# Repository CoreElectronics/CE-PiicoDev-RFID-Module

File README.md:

# PiicoDev® RFID Module

This is the repo for the Core Electronics [PiicoDev RFID Module](https://core-electronics.com.au/catalog/product/view/sku/CE08086).

The PiicoDev® RFID Module will get you started with reading (and writing) RFID tags. Use unique tag IDs to identify users, track your equipment, or make your own vending machine. Getting started is easy - there's no need for soldering, and great PiicoDev guides for Python / MicroPython. If you prefer to go freestyle, each RFID module features a standard breakout header for breadboarding or wires, and the small size makes it ideal for compact projects. This module is compatible with modern RFID / NFC tags: NTAG213, NTAG203 and Classic (aka. Mifare) tags. That means you can not only read the tag ID, but also read or write data to the tag. For more advanced projects, you can connect up to four RFID modules on a single bus. Each device address is selectable using the address switch (labelled ASW) which can select addresses from 0x2C (factory default) to 0x2F.

**Features**

- Small size to fit your project
- Read IDs and Read/Write data to your tag
- Connect up to four RFID modules on the same bus
- Great guides to get you started
- PiicoDev connector, compatible with Qwiic and STEMMA QT (3.3V only)
- 2.54mm breakout for breadboarding/prototyping
- Manufactured and supported in Australia by Core Electronics

## License
This project is open source - please review the LICENSE.md file for further licensing information.

If you have any technical questions, or concerns about licensing, please contact technical support on the [Core Electronics forums](https://forum.core-electronics.com.au/).

*\"PiicoDev\" and the PiicoDev logo are trademarks of Core Electronics Pty Ltd.*

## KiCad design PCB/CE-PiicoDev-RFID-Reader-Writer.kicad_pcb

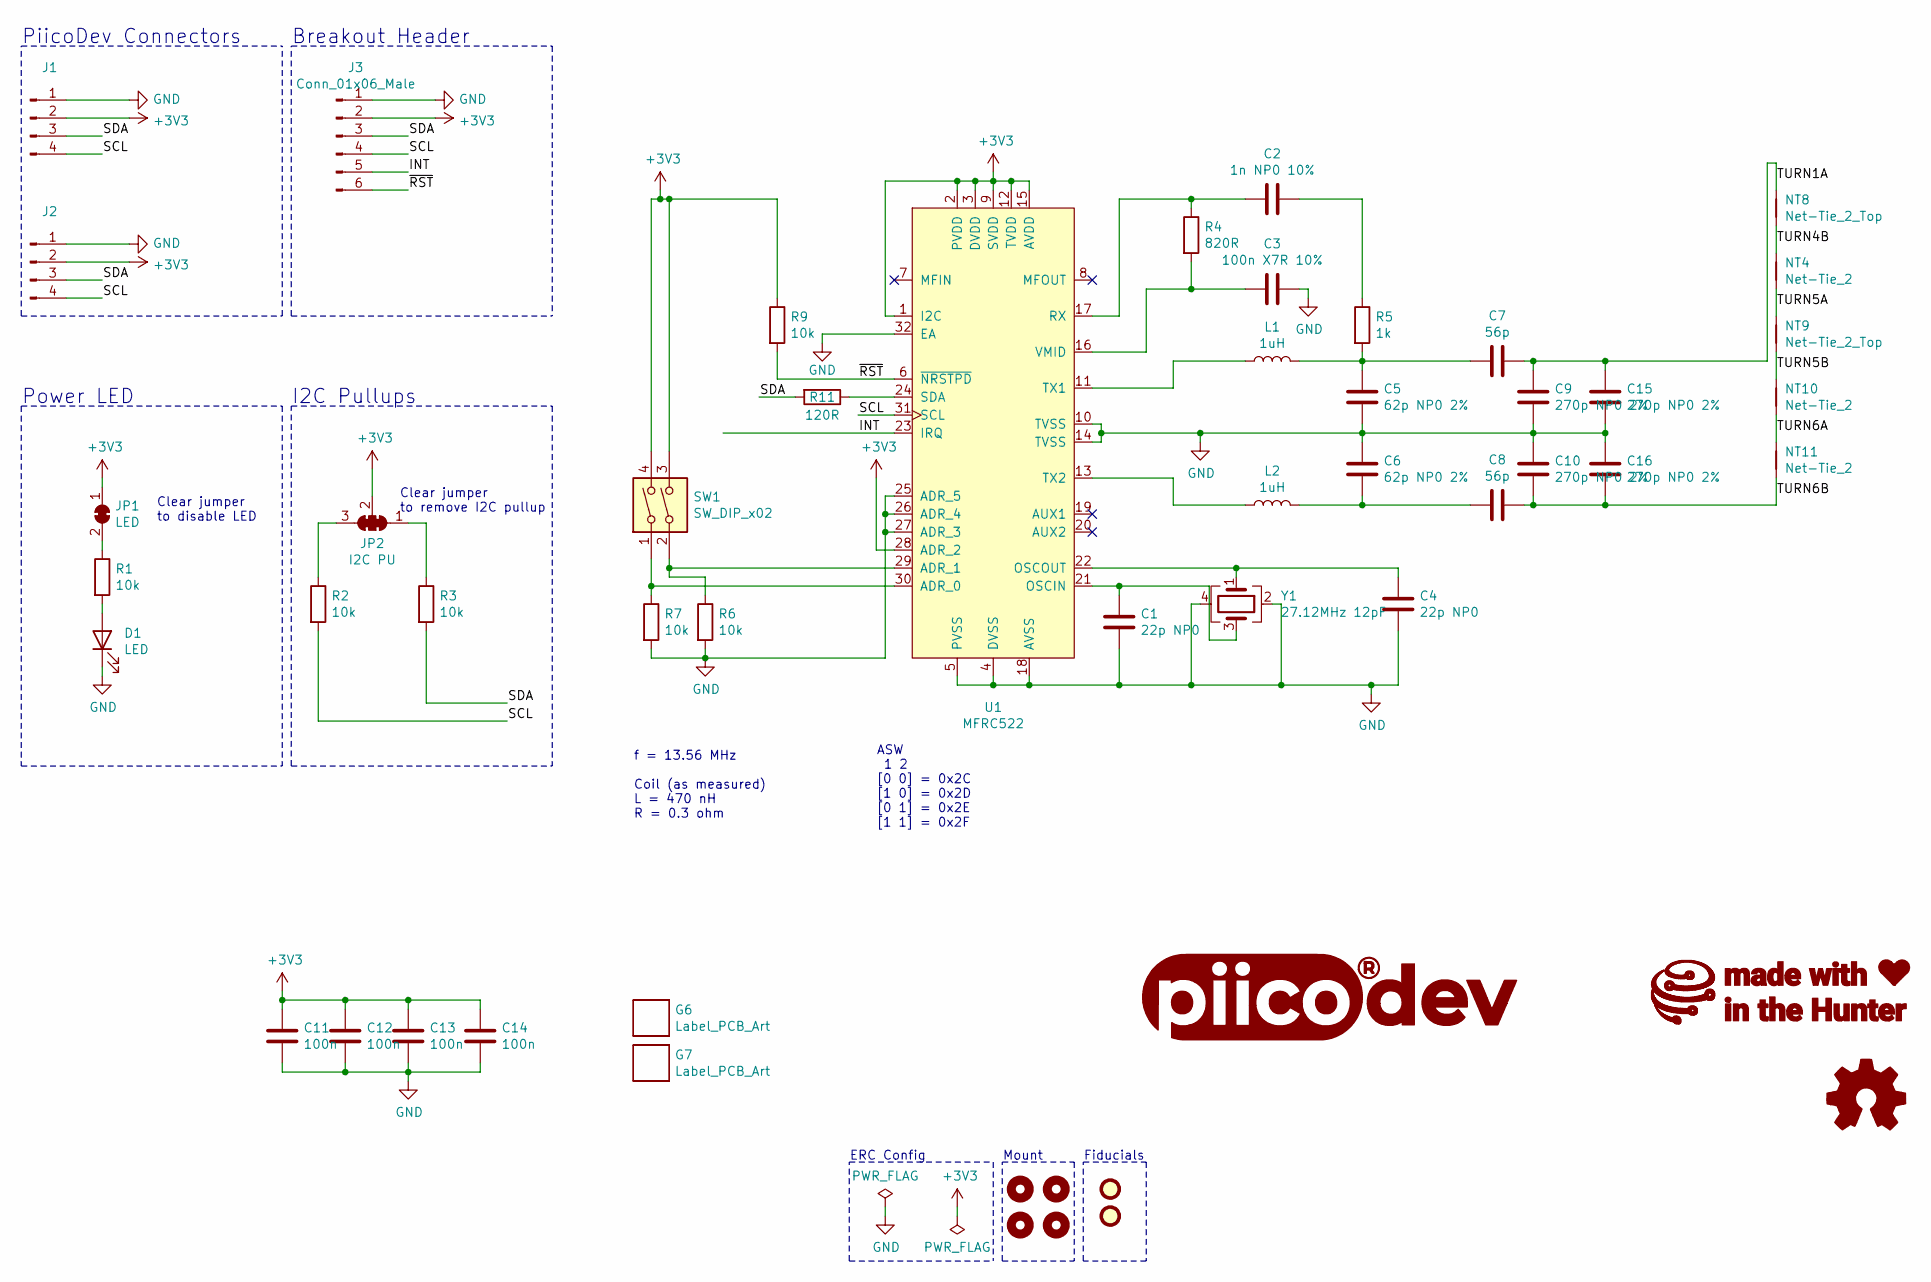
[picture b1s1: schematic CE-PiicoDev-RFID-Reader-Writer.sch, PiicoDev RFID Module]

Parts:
C1, C4: 22p NP0; C_0402_1005Metric
C2: 1n NP0 10%; C_0603_1608Metric
C3: 100n X7R 10%; C_0402_1005Metric
C5, C6: 62p NP0 2%; C_0603_1608Metric
C7, C8: 56p; C_0603_1608Metric
C9, C10, C15, C16: 270p NP0 2%; C_0603_1608Metric
C11, C12, C13, C14: 100n; C_0402_1005Metric
D1: LED; LED_0603_1608Metric
FID1, FID2: Fiducial; Fiducial_1mm_Mask2mm_No_Courtyard
G1: LOGO_PiicoDev; piicodev_logo_14.2x3.4mm
G2: LOGO_CoreElectronics_no-text
G3: LOGO_made-with-love; piicodev_logo_14.2x3.4mm
G6: Label_PCB_Art; Art_1
G7: Label_PCB_Art; Art_2
H1, H2, H3, H4: MountingHole; MountingHole_2.7mm_M2.5_PadClearance_1.2
J1, J2: JST_SH_SM04B-SRSS-TB_1x04-1MP_P1.00mm_Horizontal
J3: Conn_01x06_Male; PiicoDev_header_6pin
JP1: LED; SolderJumper-2_P1.3mm_Bridged_RoundedPad1.0x1.5mm
JP2: I2C PU; SolderJumper-3_P1.3mm_Closed_RoundedPad1.0x1.5mm_NumberLabe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
L1, L2: 1uH; L_0603_1608Metric
LOGO1: Logo_Open_Hardware_Small; oshw
NT4, NT10, NT11: Net-Tie_2; NetTie-2_SMD_Pad0.80mm
NT8, NT9: Net-Tie_2_Top; NetTie-2_SMD_Pad0.80mm
R1, R2, R3, R6, R7, R9: 10k; R_0402_1005Metric
R4: 820R; R_0603_1608Metric
R5: 1k; R_0603_1608Metric
R11: 120R; R_0402_1005Metric
SW1: SW_DIP_x02; SW_DIP_x02_Slide_CHS-02A1
U1: MFRC522; VQFN-32-1EP_5x5mm_P0.5mm_EP3.1x3.1mm_ThermalVias
Y1: 27.12MHz 12pF; Crystal_SMD_TXC_7M-4Pin_3.2x2.5mm

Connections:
+3V3: C11.1, C12.1, C13.1, C14.1, J1.2, J2.2, J3.2, JP1.1 (A), JP2.2 (C), R9.1, SW1.3, SW1.4, U1.1 (I2C), U1.2 (PVDD), U1.3 (DVDD), U1.9 (SVDD), U1.12 (TVDD), U1.15 (AVDD), U1.28 (ADR_2)
/INT: J3.5, U1.23 (IRQ)
/SCL: J1.4, J2.4, J3.4, R2.2, U1.31 (SCL)
/SDA: J1.3, J2.3, J3.3, R3.2, R11.2
/TURN1A: C7.1, C9.1, C15.1, NT8.1
/TURN4B: NT4.1, NT8.2
/TURN5A: NT4.2, NT9.1
/TURN5B: NT9.2, NT10.1
/TURN6A: NT10.2, NT11.1
/TURN6B: C8.1, C10.2, C16.2, NT11.2
/~RST: J3.6, R9.2, U1.6 (~NRSTPD); also elsewhere on the board
GND: C1.2, C3.1, C4.2, C5.2, C6.2, C9.2, C10.1, C11.2, C12.2, C13.2, C14.2, C15.2, C16.1, D1.1 (K), J1.1, J2.1, J3.1, R6.2, R7.2, U1.4 (DVSS), U1.5 (PVSS), U1.10 (TVSS), U1.14 (TVSS), U1.18 (AVSS), U1.25 (ADR_5), U1.26 (ADR_4), U1.27 (ADR_3), U1.32 (EA), Y1.2, Y1.4
unnamed: C1.1, U1.21 (OSCIN), Y1.3
unnamed: C2.1, R5.1
unnamed: C2.2, R4.1, U1.17 (RX)
unnamed: C3.2, R4.2, U1.16 (VMID)
unnamed: C4.1, U1.22 (OSCOUT), Y1.1
unnamed: C5.1, C7.2, L1.2, R5.2
unnamed: C6.1, C8.2, L2.2
unnamed: D1.2 (A), R1.2
unnamed: JP1.2 (B), R1.1
unnamed: JP2.1 (A), R3.1
unnamed: JP2.3 (B), R2.1
unnamed: L1.1, U1.11 (TX1)
unnamed: L2.1, U1.13 (TX2)
unnamed: R6.1, SW1.2, U1.29 (ADR_1)
unnamed: R7.1, SW1.1, U1.30 (ADR_0)
unnamed: R11.1, U1.24 (SDA)

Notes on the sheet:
ERC Config
Fiducials
Mount
PiicoDev Connectors
Breakout Header
Clear jumper to remove I2C pullup
I2C Pullups
Clear jumper to disable LED
Power LED
f = 13.56 MHz Coil (as measured) L = 470 nH R = 0.3 ohm
ASW 1 2 [0 0] = 0x2C [1 0] = 0x2D [0 1] = 0x2E [1 1] = 0x2F

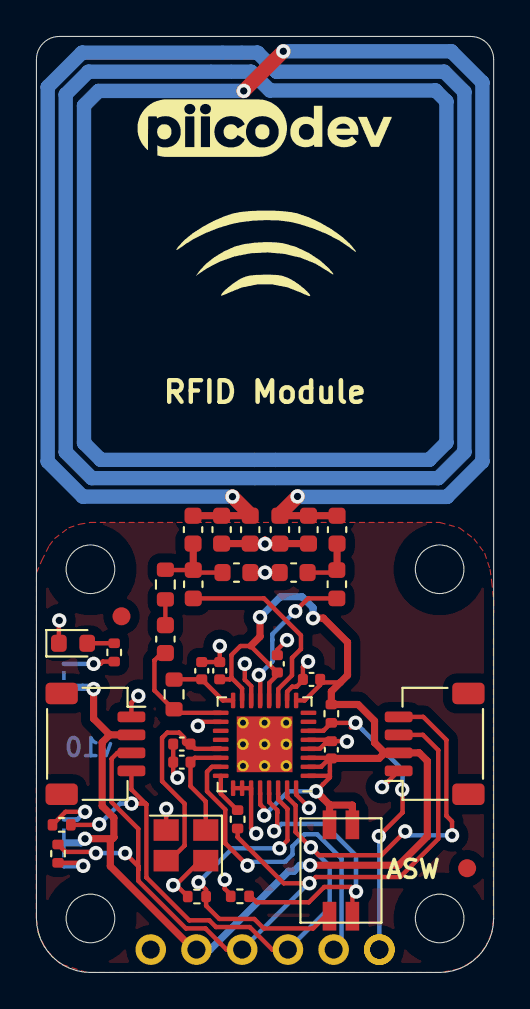
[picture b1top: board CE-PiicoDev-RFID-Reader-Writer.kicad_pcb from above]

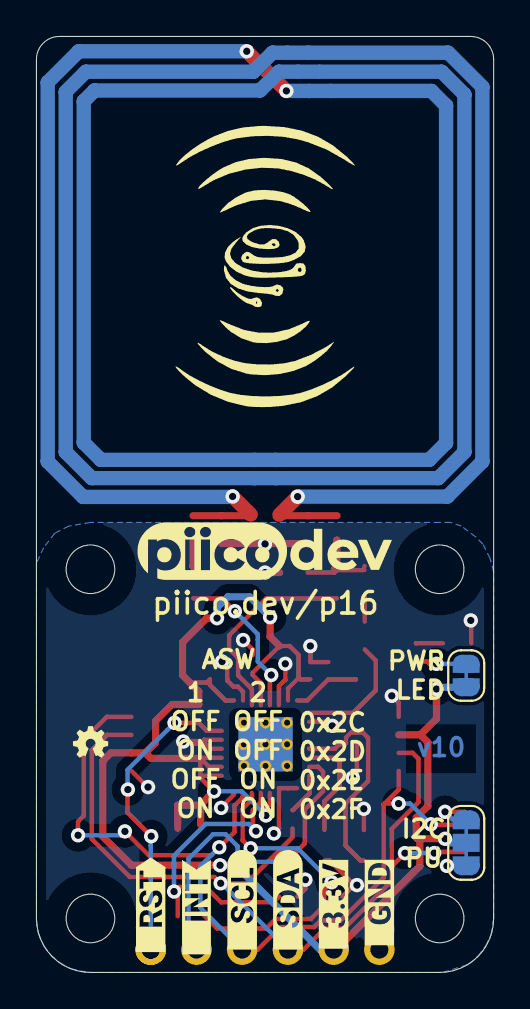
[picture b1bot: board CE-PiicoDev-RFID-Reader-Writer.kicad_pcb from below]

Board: 2 copper layers, 25.4 x 52.0 mm, 59 parts (16 on the bottom side), 28 nets.

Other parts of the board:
J4: Conn_01x01_Male; PiicoDev_header_1pin
kibuzzard-61B8280C, kibuzzard-61B8283F, kibuzzard-61B82819, kibuzzard-61B82827, kibuzzard-61B82831, kibuzzard-61B82849: G***; label

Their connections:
/~RST: J4.1; also elsewhere on the board

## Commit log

2021-09-08 Update all
2021-09-16 Add R10
2021-11-11 Change v00 to v01
    Halve the coil length.
    Make wider coil tracks.
    Add test points.
    Add I2C series resistor.
    Change inductors from 0402 to 0603.
2021-12-07 Improve Artwork
2021-12-14 Remove Interrupt LED and add DIP switches
2021-12-15 Rename Project
2021-12-21 Move via from directly under C14
2021-12-23 Update DIP Switch Footprint
2022-01-06 Update PCB jumpers with thinner cut trace
2022-01-12 v10 Release
    Remove testpoints
    Change ASW order so SW1 is LSB
2022-01-13 Move coil down 0.2mm
    Avoids issues with V-Cuts
2022-01-13 Change R5 to 1k
2022-03-14 Add schematic.pdf and schematic comments

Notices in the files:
PCB/CE-PiicoDev-RFID-Reader-Writer.sch:
License: CCASAv4.0 http://creativecommons.org/licenses/by-sa/4.0
